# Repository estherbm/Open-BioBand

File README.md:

# Open-BioBand

    Open BioBand is a biometric Open Source wristband with BLE (Bluetooth
    Low Energy) connectivity used to non-invasive monitorization of patients
    and their environment. It measure several parameters such as pulse, SPO2,
    body temperature, motion activity, pressure, humidity, temperature...

    It allow developers to investigate and learn about wearables and biometric 
    sensors and artists to create new biological performances and projects.
    
    Created as final thesis Industrial Engineering project.

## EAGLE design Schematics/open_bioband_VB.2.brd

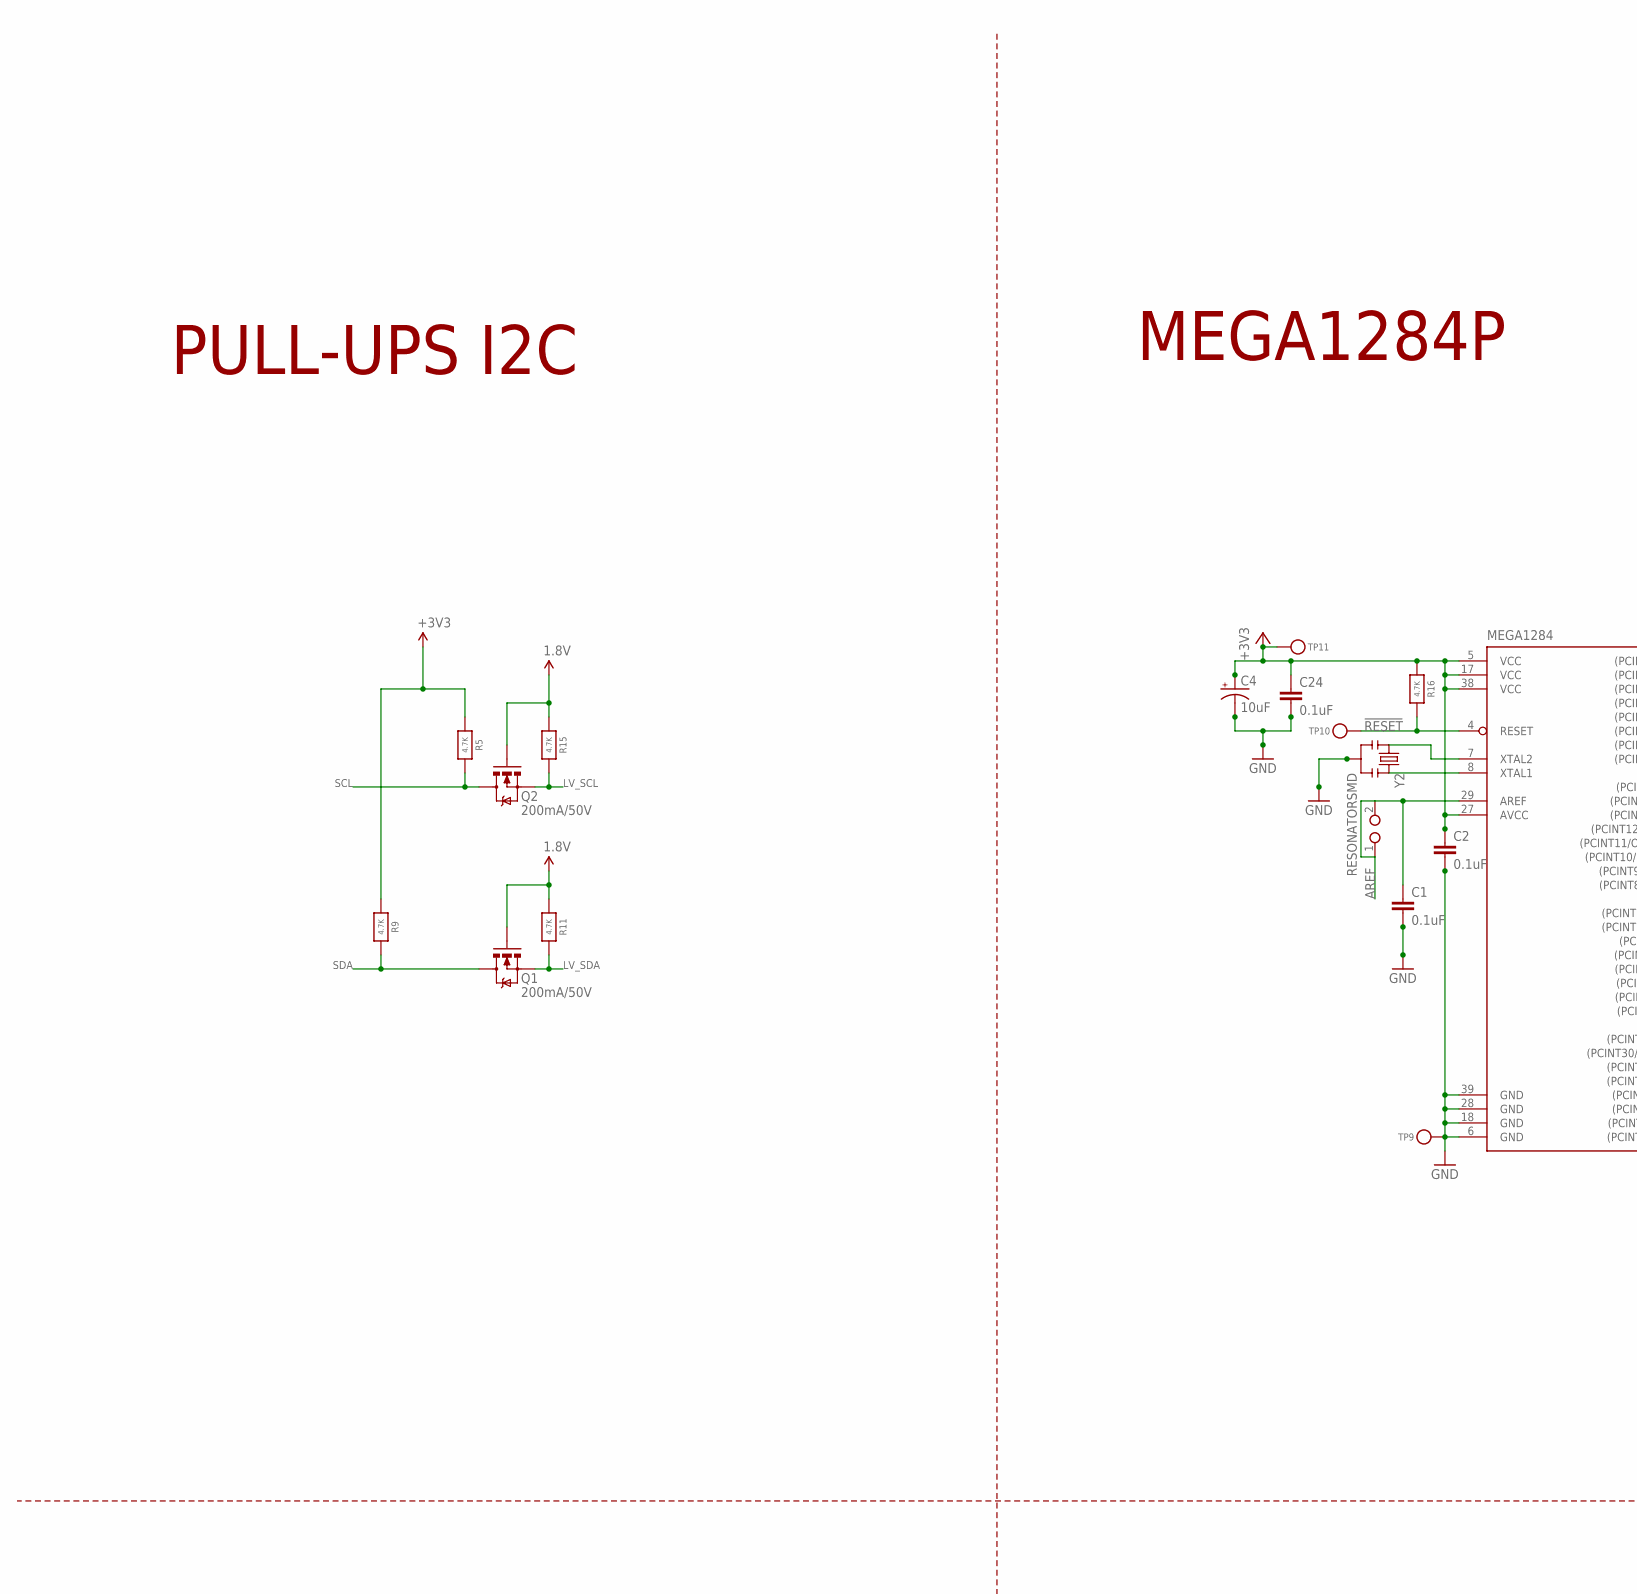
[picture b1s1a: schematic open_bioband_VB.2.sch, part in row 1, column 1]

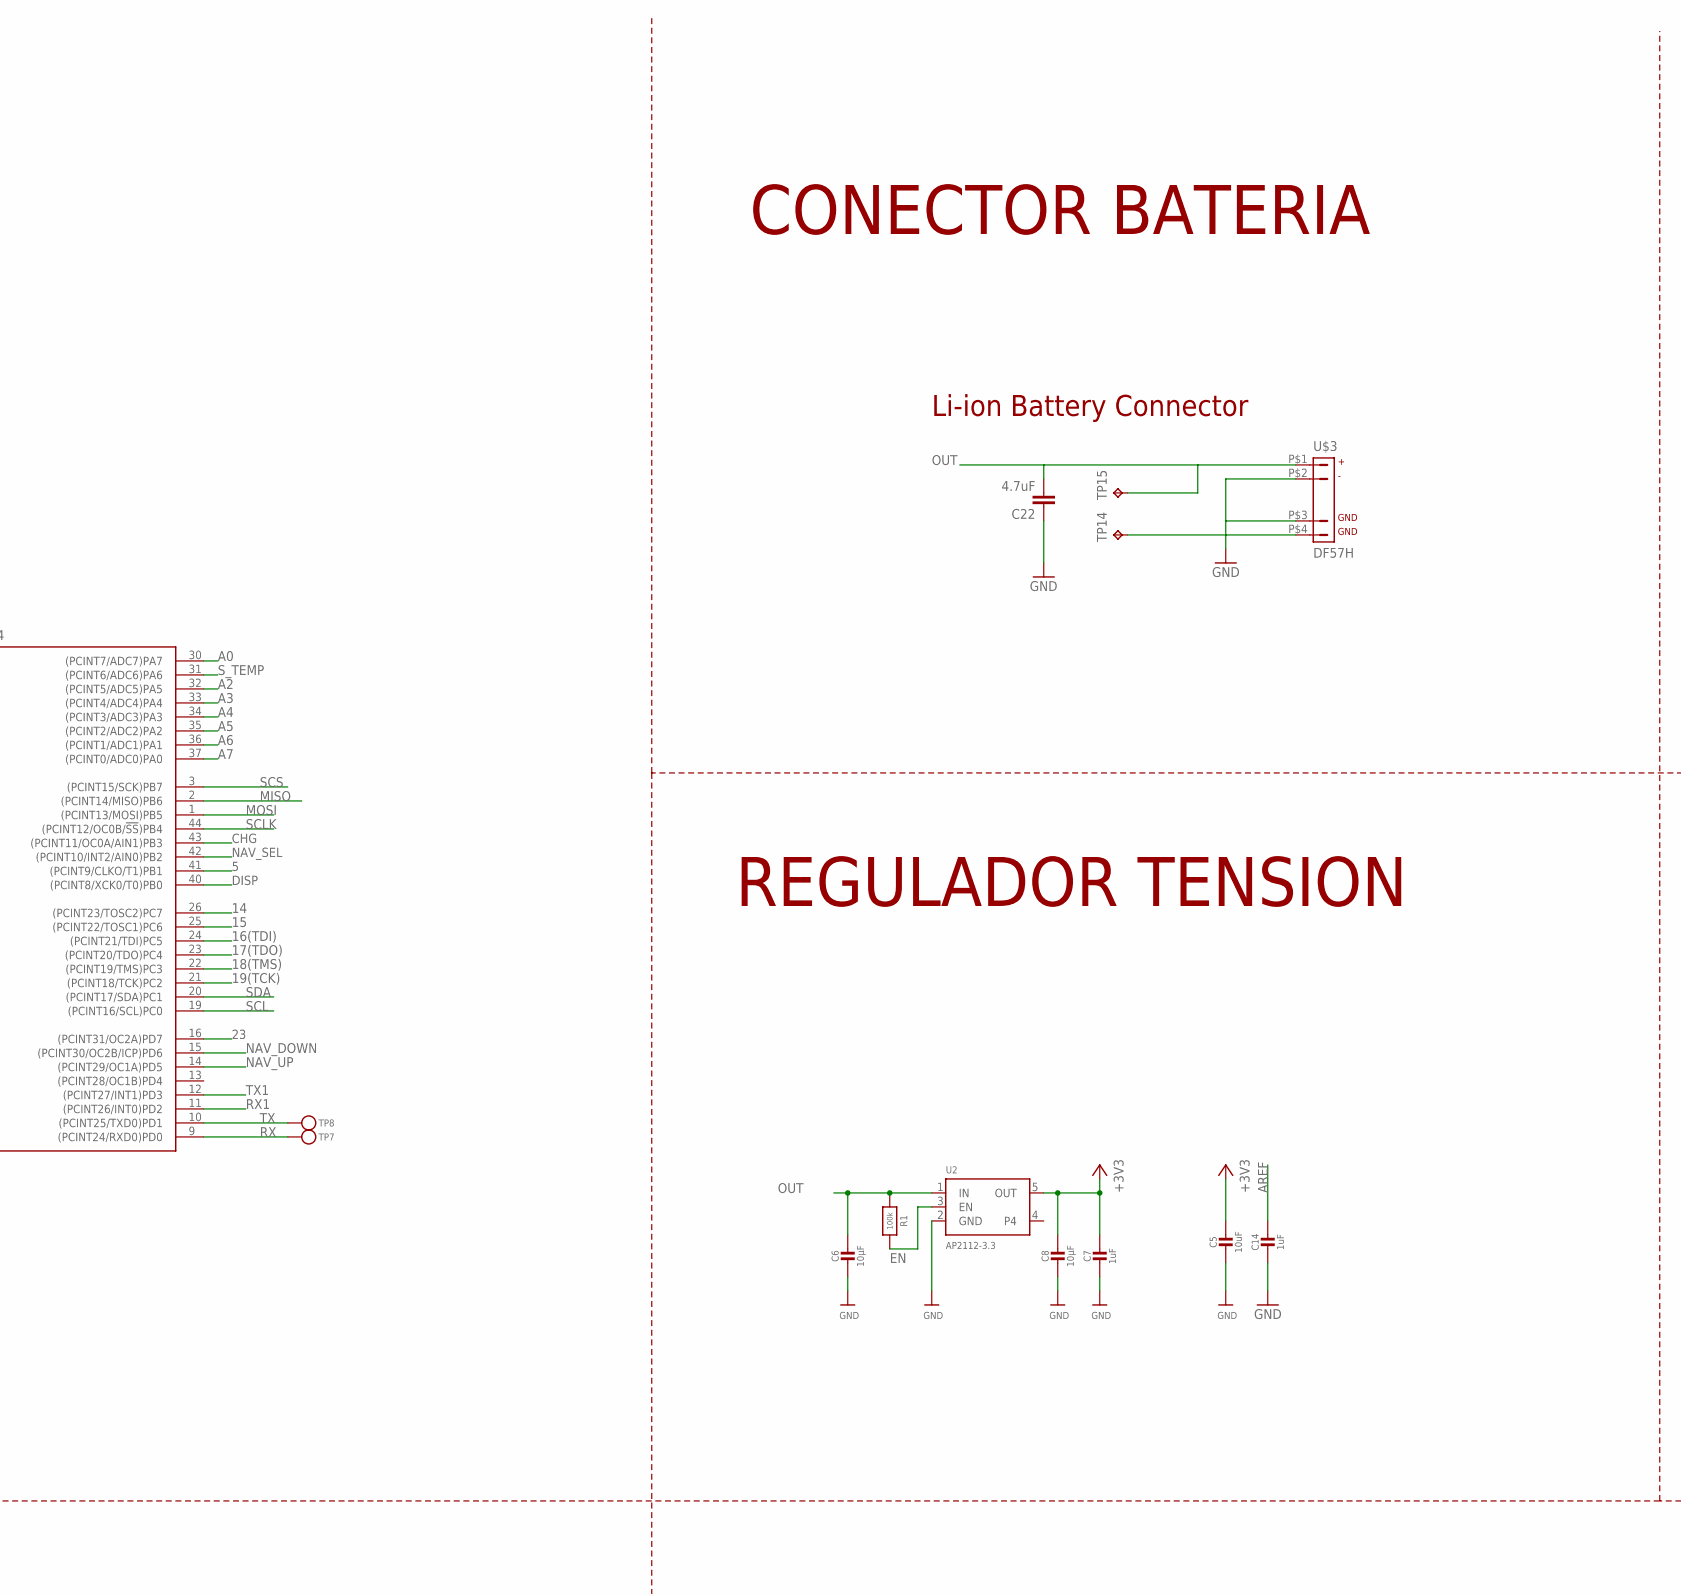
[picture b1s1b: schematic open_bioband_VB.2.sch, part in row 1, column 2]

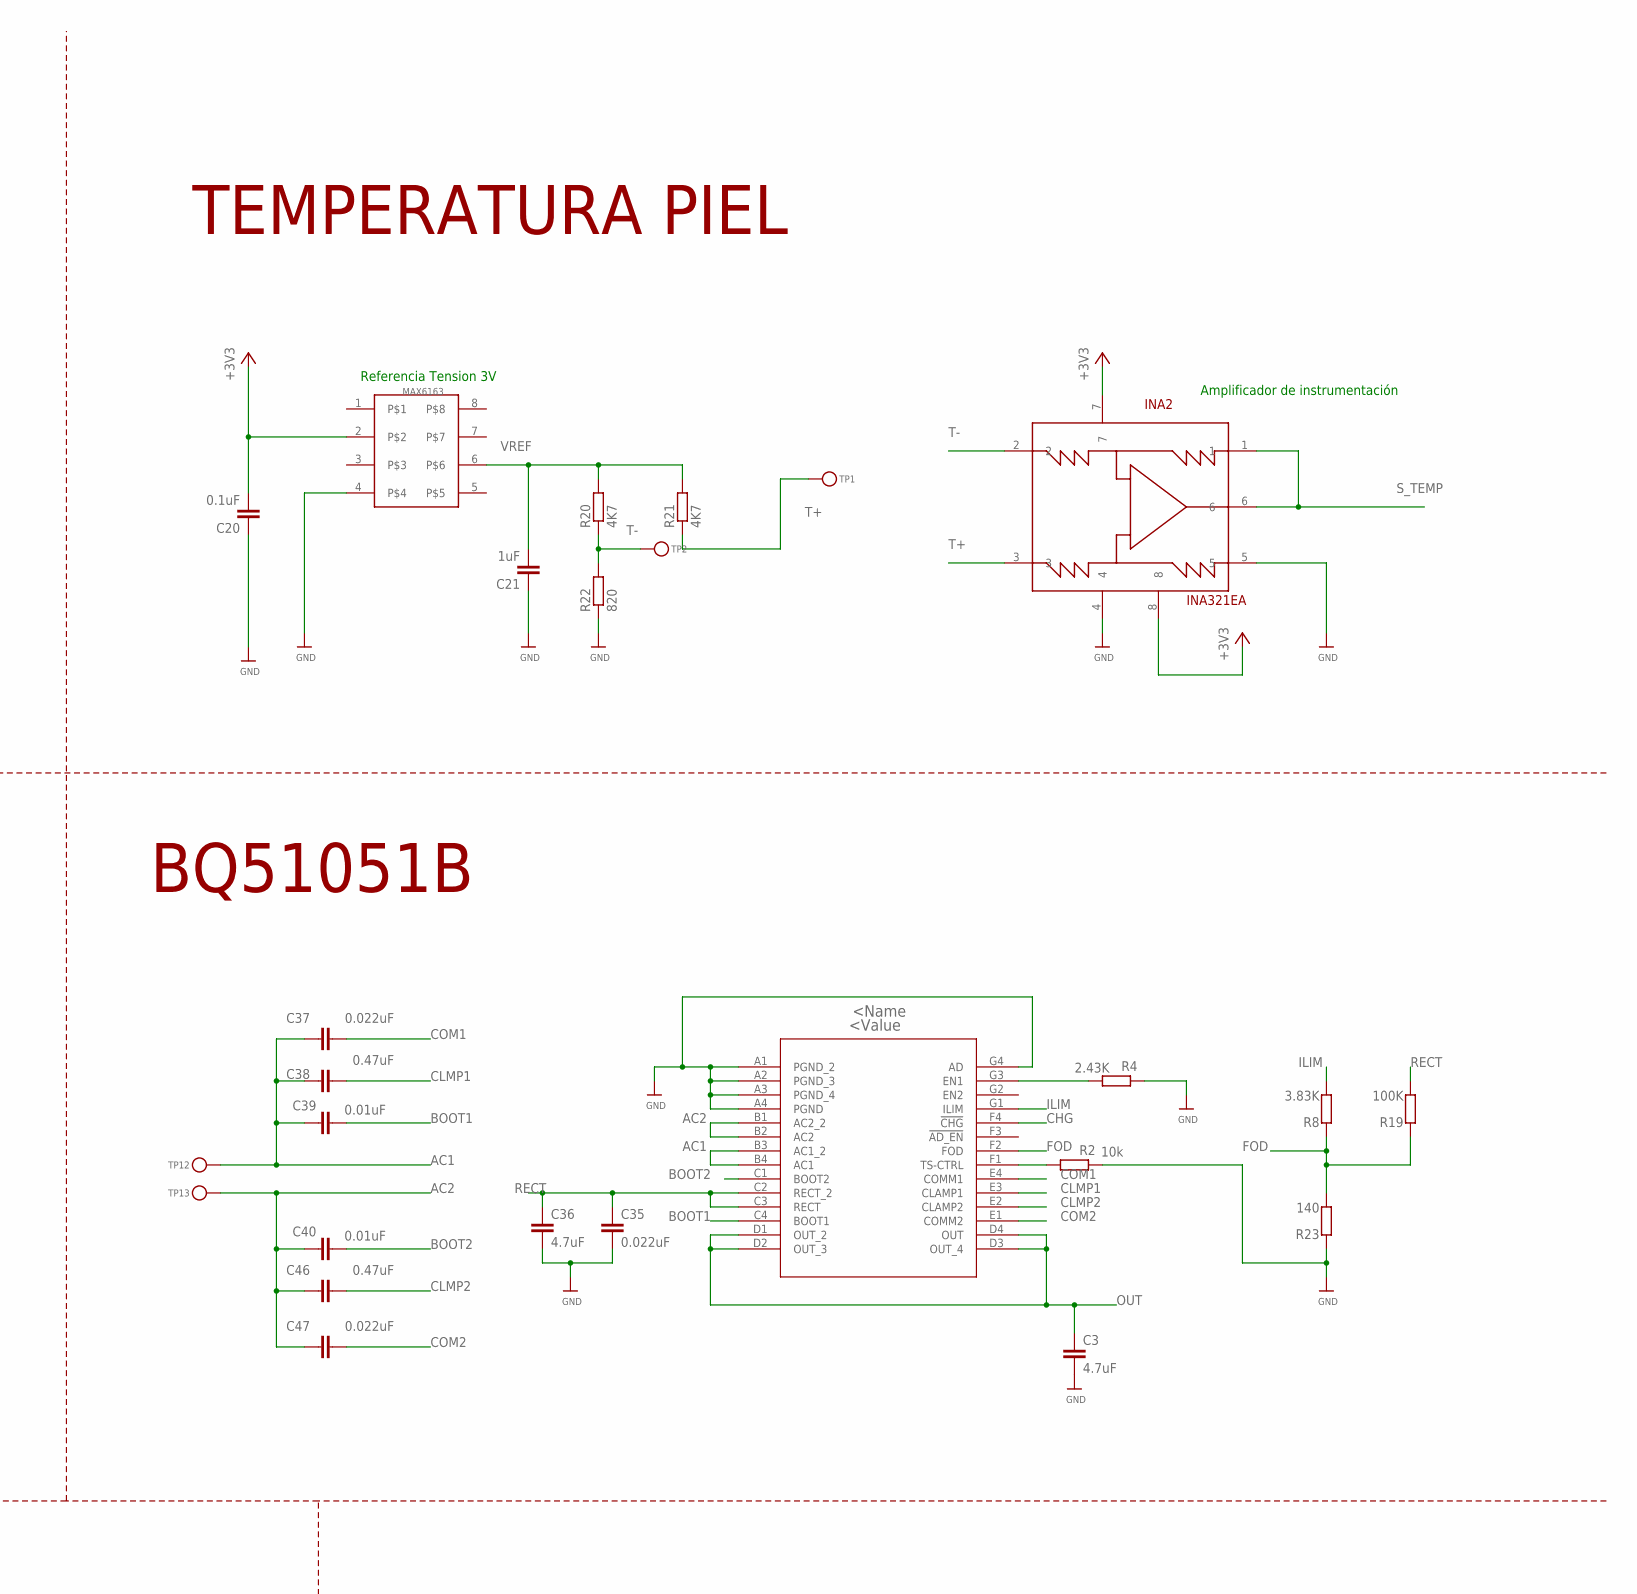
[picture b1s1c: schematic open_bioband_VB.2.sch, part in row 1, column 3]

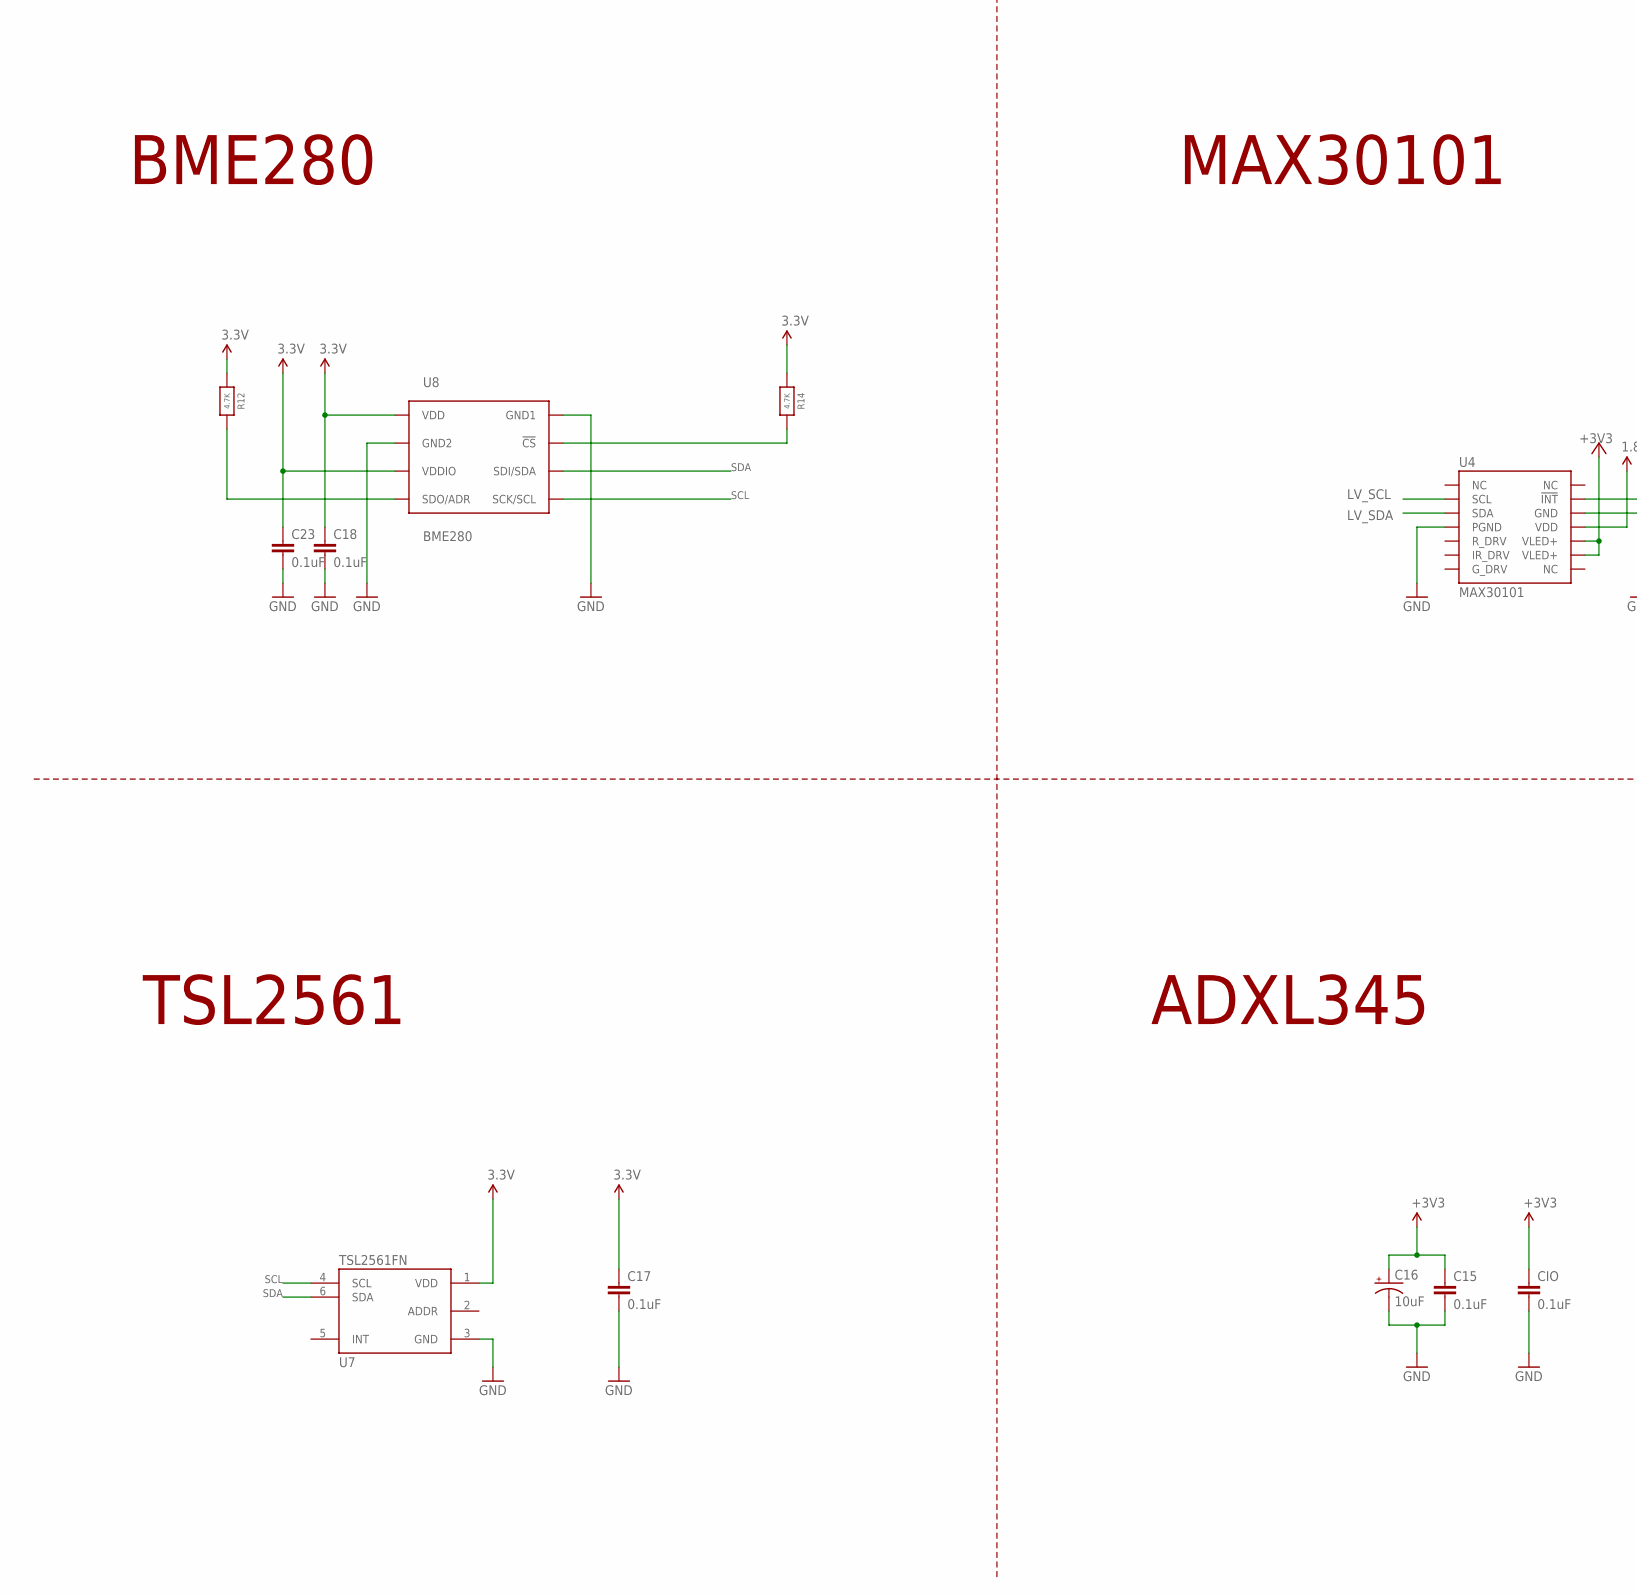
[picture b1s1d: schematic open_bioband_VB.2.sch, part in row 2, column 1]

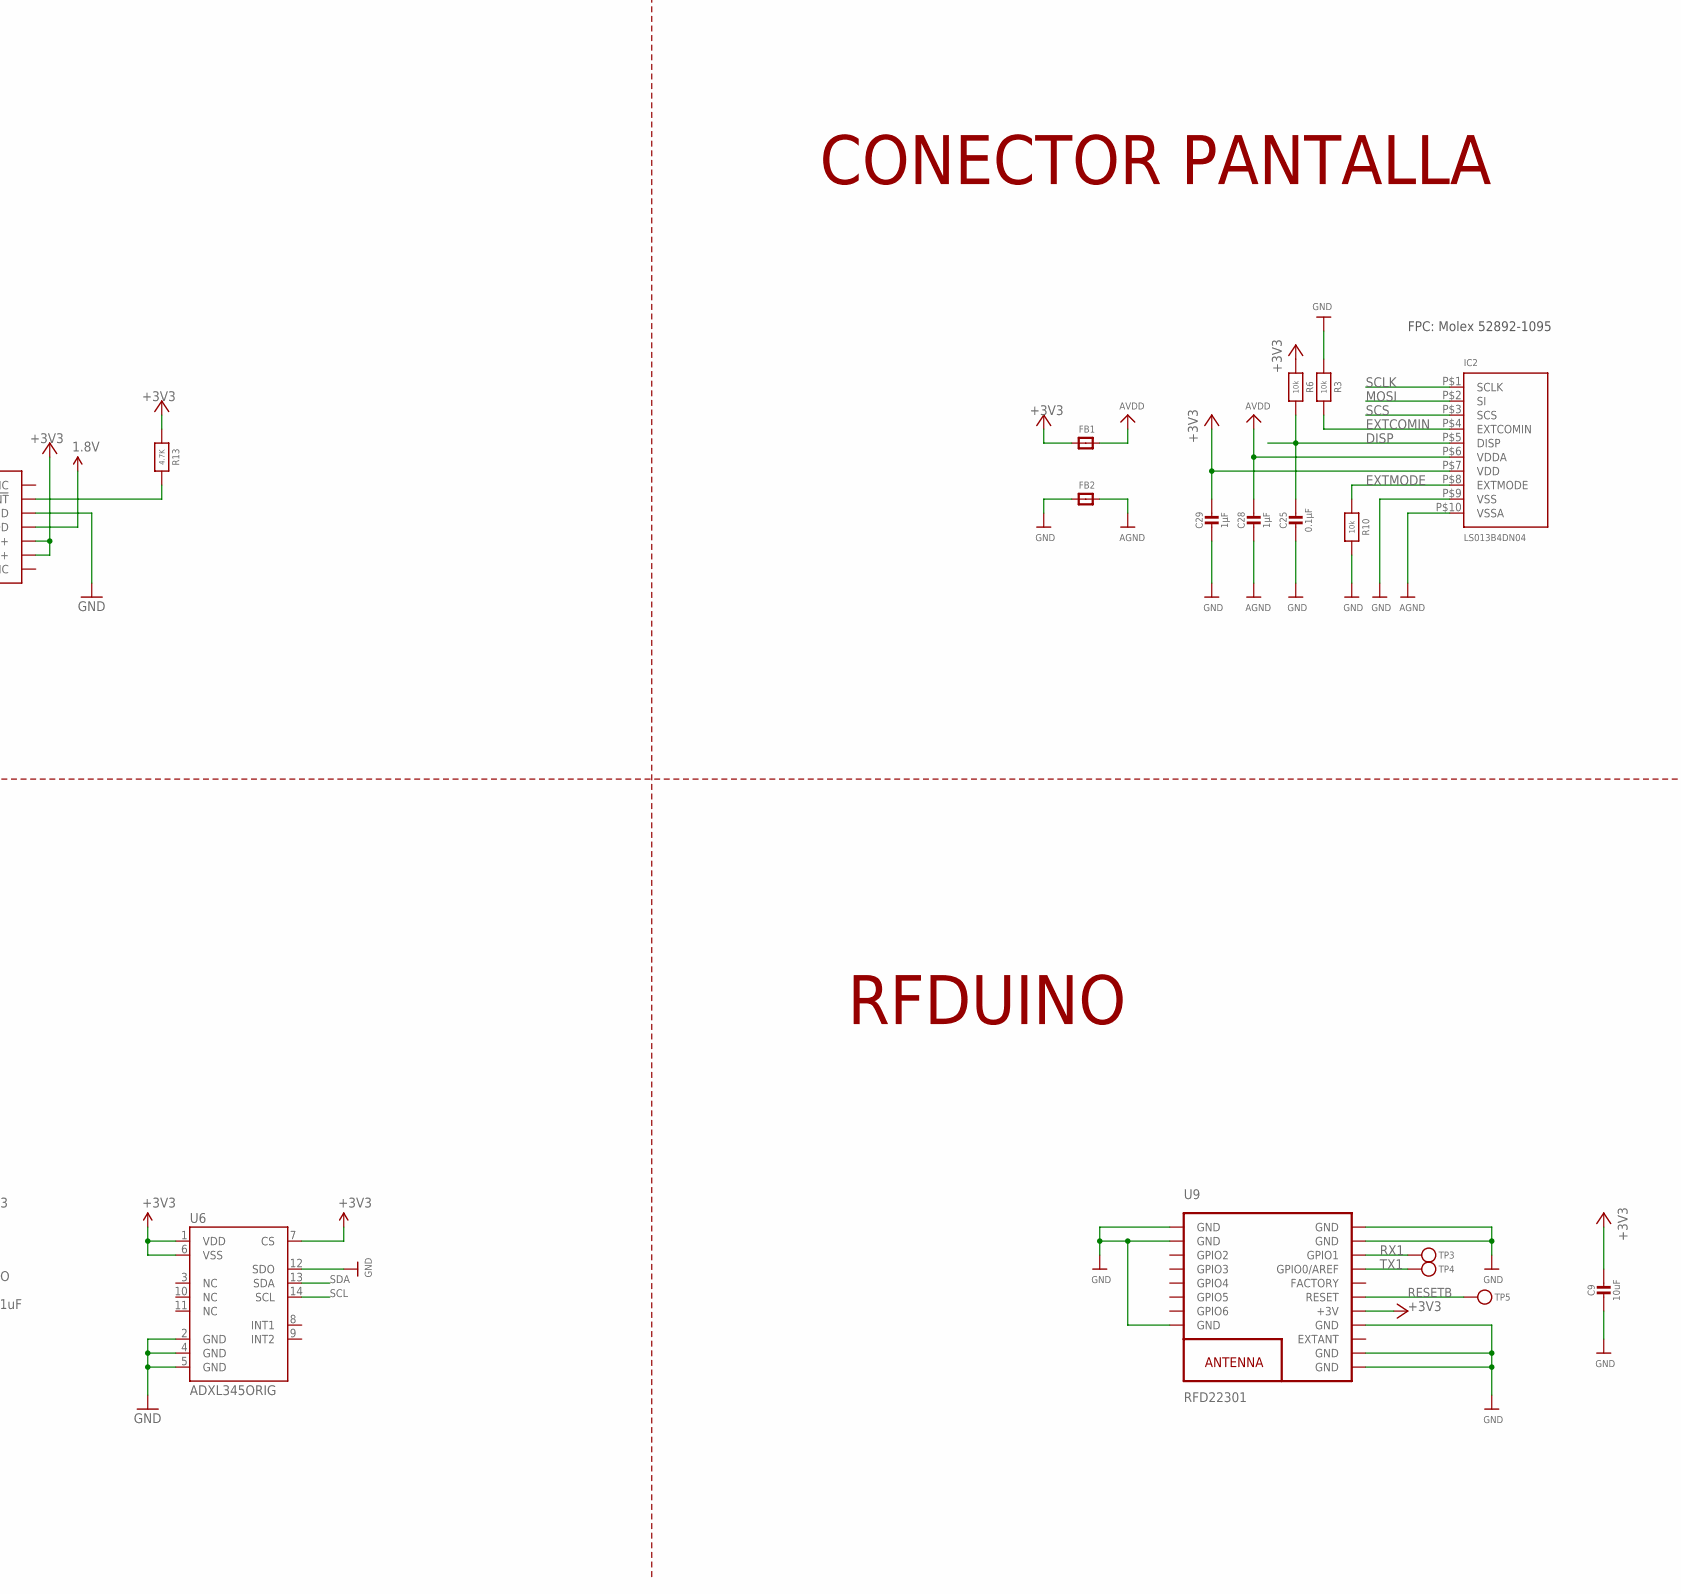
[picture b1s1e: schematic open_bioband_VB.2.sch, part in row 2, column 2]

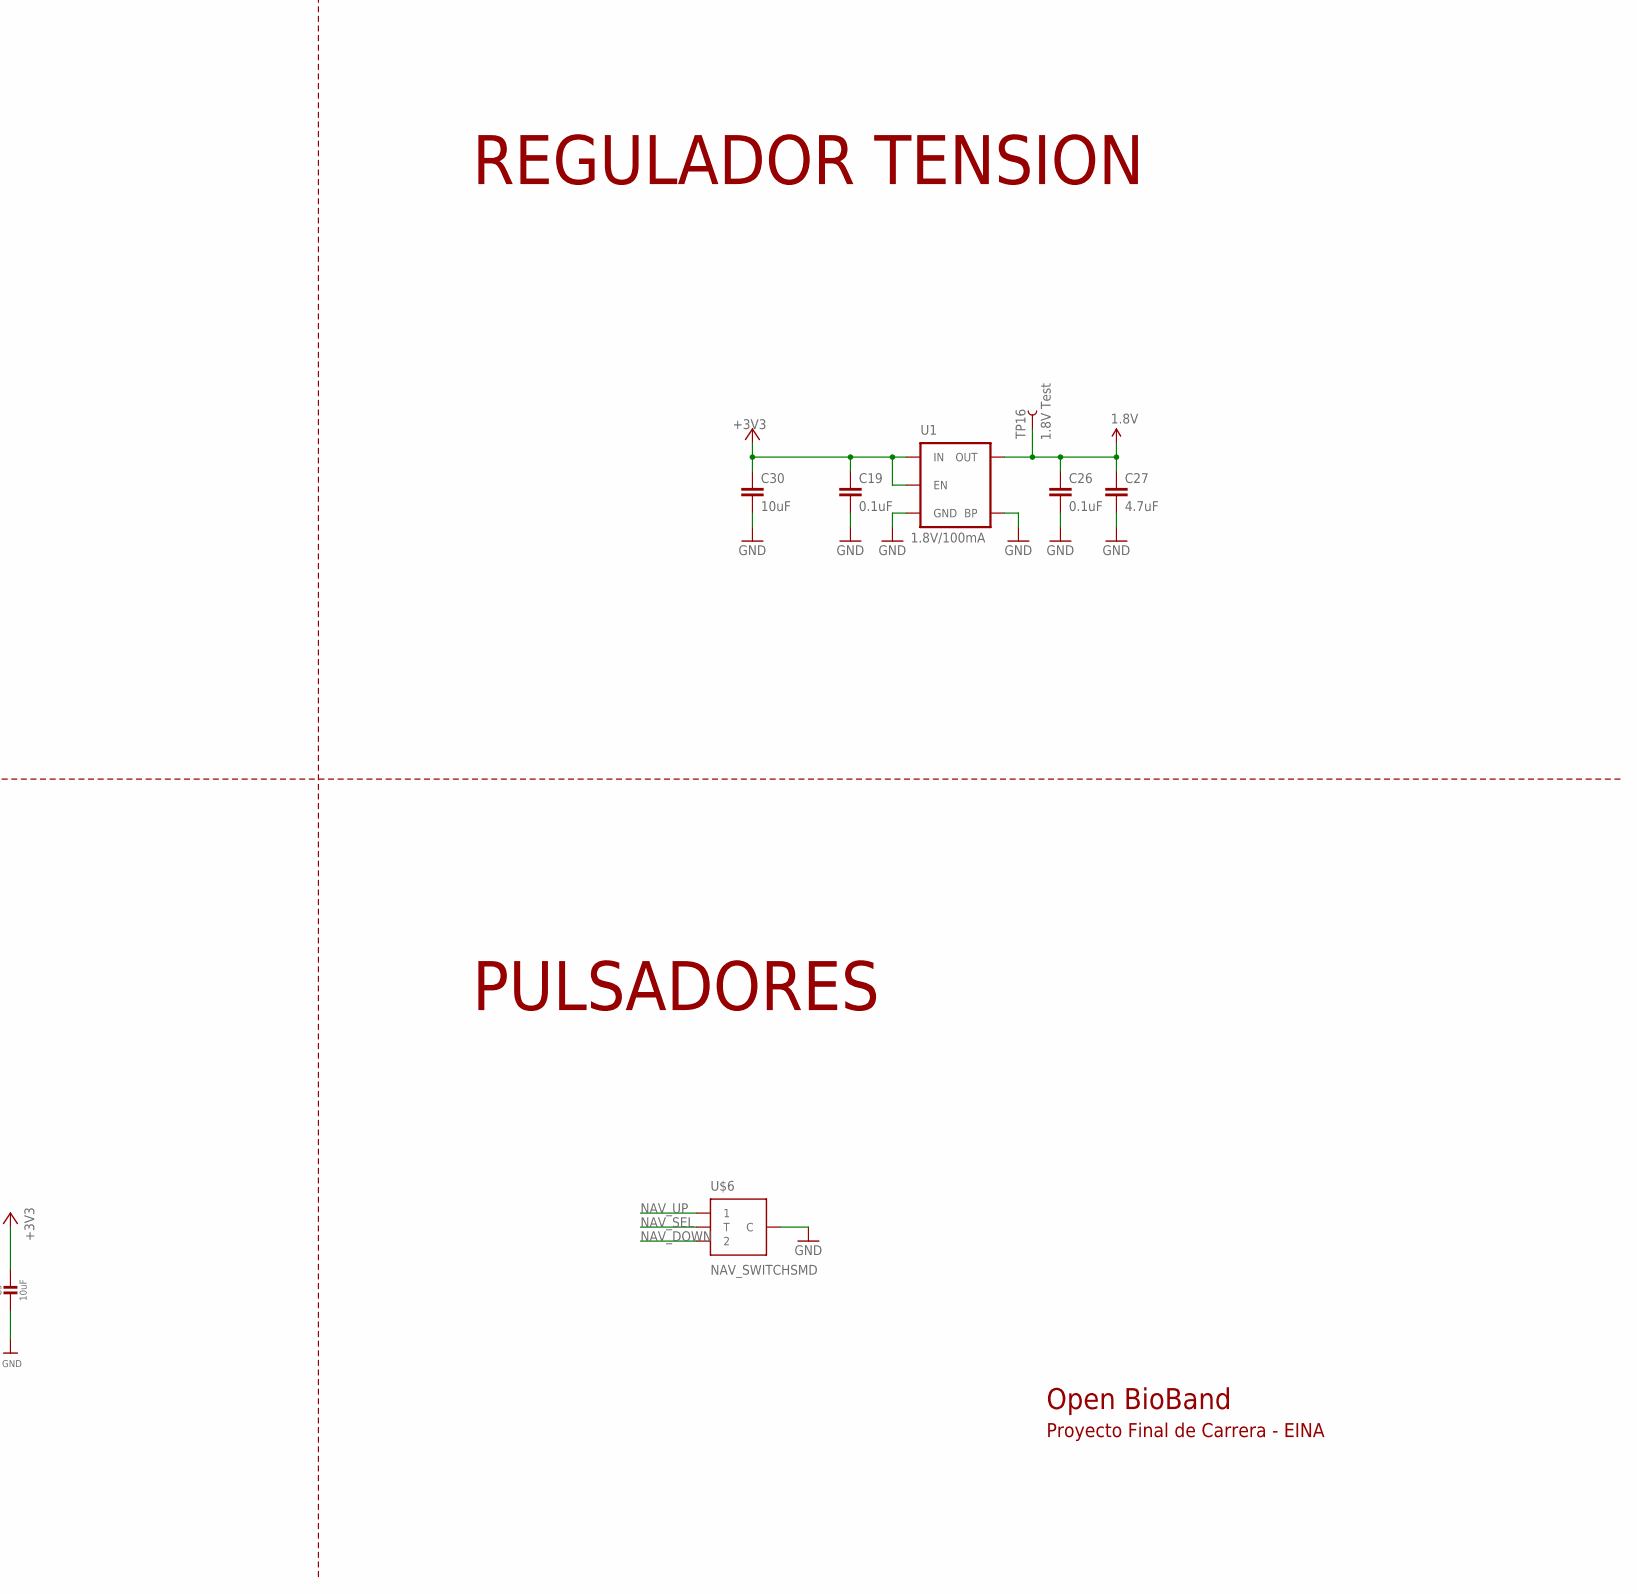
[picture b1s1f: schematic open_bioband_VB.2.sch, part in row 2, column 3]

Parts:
C1, C2, C15, C17, C18, C19, C23, C24, C26: 0.1uF; 0402-CAP
C3, C22, C36: 4.7uF; C0402
C4, C16: 10uF; EIA3216
C5, C9: 10uF; _0402
C6, C8: 10µF; _0402
C7, C14: 1uF; _0402
C20: 0.1uF; C0402
C21: 1uF; C0402
C25: 0.1µF; _0402
C27: 4.7uF; 0402-CAP
C28, C29: 1µF; _0402
C30: 10uF; 0402-CAP
C35, C37, C47: 0.022uF; C0402
C38, C46: 0.47uF; C0402
C39, C40: 0.01uF; C0402
CIO: 0.1uF; 0402-CAP
FB1, FB2: FERRITE_0402; _0402
IC2: LS013B4DN04; FPC_10PIN_52892-1095
INA2: INA321EA; MSOP08
MAX1: MAX6163; SO08
MEGA1284: ATMEGA644A; TQFP44
Q1, Q2: 200mA/50V; SOT23-3
R1: 100k; _0402
R2: 10k; R0402
R3, R6, R10: 10k; _0402
R4: 2.43K; R0402
R5, R9, R11, R12, R13, R14, R15, R16: 4.7K; _0402
R8: 3.83K; R0402
R19: 100K; R0402
R20, R21: 4K7; R0402
R22: 820; R0402
R23: 140; R0402
TP1, TP2, TP3, TP4, TP5, TP7, TP8, TP9, TP10, TP11, TP12, TP13: TESTPOINTROUND1.5MM; TESTPOINT_ROUND_1.5MM
TP14, TP15: TPB1,27; B1,27
TP16: 1.8V Test; PAD.03X.04
U1: 1.8V/100mA; SC70
U2: AP2112-3.3; SOT23-5
U3: BQ51003YFPT; YFP28
U4: MAX30101; OLGA-14
U6: ADXL345ORIG; LGA14
U7: TSL2561FN; FN-6
U8: BME280; BME280_LGA
U9: RFD22301
U$3: DF57H; DF57H-2P
U$5: JUMPER1-1
U$6: NAV_SWITCHSMD; NAV_SWITCH
Y2: RESONATORSMD; RESONATOR-SMD

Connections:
1.8V: C26.1, C27.1, Q1.1 (G), Q2.1 (G), R11.1, R15.1, TP16.P$1, U1.5 (OUT), U4.11 (VDD)
5: MEGA1284.41 ((PCINT9/CLKO/T1)PB1)
14: MEGA1284.26 ((PCINT23/TOSC2)PC7)
15: MEGA1284.25 ((PCINT22/TOSC1)PC6)
16(TDI): MEGA1284.24 ((PCINT21/TDI)PC5)
17(TDO): MEGA1284.23 ((PCINT20/TDO)PC4)
18(TMS): MEGA1284.22 ((PCINT19/TMS)PC3)
19(TCK): MEGA1284.21 ((PCINT18/TCK)PC2)
23: MEGA1284.16 ((PCINT31/OC2A)PD7)
!CS: R14.2, U8.P$2 (!CS)
!INT: R13.2, U4.13 (!INT)
!RESET: MEGA1284.4 (RESET), R16.2, TP10.P$1
+3V3: C2.1, C4.A (+), C5.1, C7.1, C8.1, C9.1, C15.1, C16.A (+), C17.1, C19.1, C20.2, C24.1, C29.1, C30.1, CIO.1, FB1.1, IC2.P$7 (VDD), INA2.7, INA2.8, MAX1.2, MEGA1284.5 (VCC), MEGA1284.17 (VCC), MEGA1284.27 (AVCC), MEGA1284.38 (VCC), R5.1, R6.1, R9.1, R13.1, R16.1, TP11.P$1, U1.1 (IN), U1.3 (EN), U2.5 (OUT), U4.9 (VLED+), U4.10 (VLED+), U6.1 (VDD), U6.6 (VSS), U6.7 (CS), U7.1 (VDD), U9.13 (+3V)
A0: MEGA1284.30 ((PCINT7/ADC7)PA7)
A2: MEGA1284.32 ((PCINT5/ADC5)PA5)
A3: MEGA1284.33 ((PCINT4/ADC4)PA4)
A4: MEGA1284.34 ((PCINT3/ADC3)PA3)
A5: MEGA1284.35 ((PCINT2/ADC2)PA2)
A6: MEGA1284.36 ((PCINT1/ADC1)PA1)
A7: MEGA1284.37 ((PCINT0/ADC0)PA0)
AC1: C37.1, C38.1, C39.1, TP12.P$1, U3.B3 (AC1_2), U3.B4 (AC1)
AC2: C40.1, C46.1, C47.1, TP13.P$1, U3.B1 (AC2_2), U3.B2 (AC2)
AGND: C28.2, FB2.2, IC2.P$10 (VSSA)
AREF: C1.1, C14.1, MEGA1284.29 (AREF), U$5.1, U$5.2
AVDD: C28.1, FB1.2, IC2.P$6 (VDDA)
BOOT1: C39.2, U3.C4 (BOOT1)
BOOT2: C40.2, U3.C1 (BOOT2)
CHG: MEGA1284.43 ((PCINT11/OC0A/AIN1)PB3), U3.F4 (!CHG)
CLMP1: C38.2, U3.E3 (CLAMP1)
CLMP2: C46.2, U3.E2 (CLAMP2)
COM1: C37.2, U3.E4 (COMM1)
COM2: C47.2, U3.E1 (COMM2)
DISP: C25.1, IC2.P$5 (DISP), MEGA1284.40 ((PCINT8/XCK0/T0)PB0), R6.2
EN: R1.2, U2.3 (EN)
EXTCOMIN: IC2.P$4 (EXTCOMIN), R3.2
EXTMODE: IC2.P$8 (EXTMODE), R10.1
FOD: R8.1, R19.1, R23.2, U3.F2 (FOD)
GND: C1.2, C2.2, C3.2, C4.C (-), C5.2, C6.2, C7.2, C8.2, C9.2, C14.2, C15.2, C16.C (-), C17.2, C18.2, C19.2, C20.1, C21.1, C22.1, C23.2, C24.2, C25.2, C26.2, C27.2, C29.2, C30.2, C35.2, C36.2, CIO.2, FB2.1, IC2.P$9 (VSS), INA2.4, INA2.5, MAX1.4, MEGA1284.6 (GND), MEGA1284.18 (GND), MEGA1284.28 (GND), MEGA1284.39 (GND), R2.2, R3.1, R4.2, R10.2, R22.1, R23.1, TP9.P$1, TP14.TP, U1.2 (GND), U1.4 (BP), U2.2 (GND), U3.A1 (PGND_2), U3.A2 (PGND_3), U3.A3 (PGND_4), U3.A4 (PGND), U3.G4 (AD), U4.4 (PGND), U4.12 (GND), U6.2 (GND), U6.4 (GND), U6.5 (GND), U6.12 (SDO), U7.3 (GND), U8.P$1 (GND1), U8.P$7 (GND2), U9.1 (GND), U9.2 (GND), U9.8 (GND), U9.9 (GND), U9.10 (GND), U9.12 (GND), U9.18 (GND), U9.19 (GND), U$3.P$2 (2), U$3.P$3 (5), U$3.P$4 (6), U$6.C, Y2.2
ILIM: R8.2, U3.G1 (ILIM)
LV_SCL: Q2.2 (S), R15.2, U4.2 (SCL)
LV_SDA: Q1.2 (S), R11.2, U4.3 (SDA)
MISO: MEGA1284.2 ((PCINT14/MISO)PB6)
MOSI: IC2.P$2 (SI), MEGA1284.1 ((PCINT13/MOSI)PB5)
unnamed: MEGA1284.7 (XTAL2), Y2.1
unnamed: R4.1, U3.G3 (EN1)
unnamed: MEGA1284.8 (XTAL1), Y2.3
unnamed: R2.1, U3.F1 (TS-CTRL)
NAV_DOWN: MEGA1284.15 ((PCINT30/OC2B/ICP)PD6), U$6.2
NAV_SEL: MEGA1284.42 ((PCINT10/INT2/AIN0)PB2), U$6.T
NAV_UP: MEGA1284.14 ((PCINT29/OC1A)PD5), U$6.1
OUT: C3.1, C6.1, C22.2, R1.1, TP15.TP, U2.1 (IN), U3.D1 (OUT_2), U3.D2 (OUT_3), U3.D3 (OUT_4), U3.D4 (OUT), U$3.P$1 (1)
RECT: C35.1, C36.1, R19.2, U3.C2 (RECT_2)
RESETB: TP5.P$1, U9.14 (RESET)
RX: MEGA1284.9 ((PCINT24/RXD0)PD0), TP7.P$1
RX1: MEGA1284.11 ((PCINT26/INT0)PD2), TP3.P$1, U9.17 (GPIO1)
SCL: MEGA1284.19 ((PCINT16/SCL)PC0), Q2.3 (D), R5.2, U6.14 (SCL), U7.4 (SCL), U8.P$4 (SCK/SCL)
SCLK: IC2.P$1 (SCLK), MEGA1284.44 ((PCINT12/OC0B/!SS!)PB4)
SCS: IC2.P$3 (SCS), MEGA1284.3 ((PCINT15/SCK)PB7)
SDA: MEGA1284.20 ((PCINT17/SDA)PC1), Q1.3 (D), R9.2, U6.13 (SDA), U7.6 (SDA), U8.P$3 (SDI/SDA)
SDO/ADR: R12.2, U8.P$5 (SDO/ADR)
S_TEMP: INA2.1, INA2.6, MEGA1284.31 ((PCINT6/ADC6)PA6)
T+: INA2.3, R21.1, TP1.P$1
T-: INA2.2, R20.1, R22.2, TP2.P$1
TX: MEGA1284.10 ((PCINT25/TXD0)PD1), TP8.P$1
TX1: MEGA1284.12 ((PCINT27/INT1)PD3), TP4.P$1, U9.16 (GPIO0/AREF)
VCC: C18.1, C23.1, R12.1, R14.1, U8.P$6 (VDDIO), U8.P$8 (VDD)
VREF: C21.2, MAX1.6, R20.2, R21.2

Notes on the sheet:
FPC: Molex 52892-1095
Referencia Tension 3V
Amplificador de instrumentación
Li-ion Battery Connector
Open BioBand
Proyecto Final de Carrera - EINA
TSL2561
ADXL345
RFDUINO
MAX30101
CONECTOR PANTALLA
BME280
REGULADOR TENSION
PULL-UPS I2C
MEGA1284P
CONECTOR BATERIA
BQ51051B
TEMPERATURA PIEL
PULSADORES

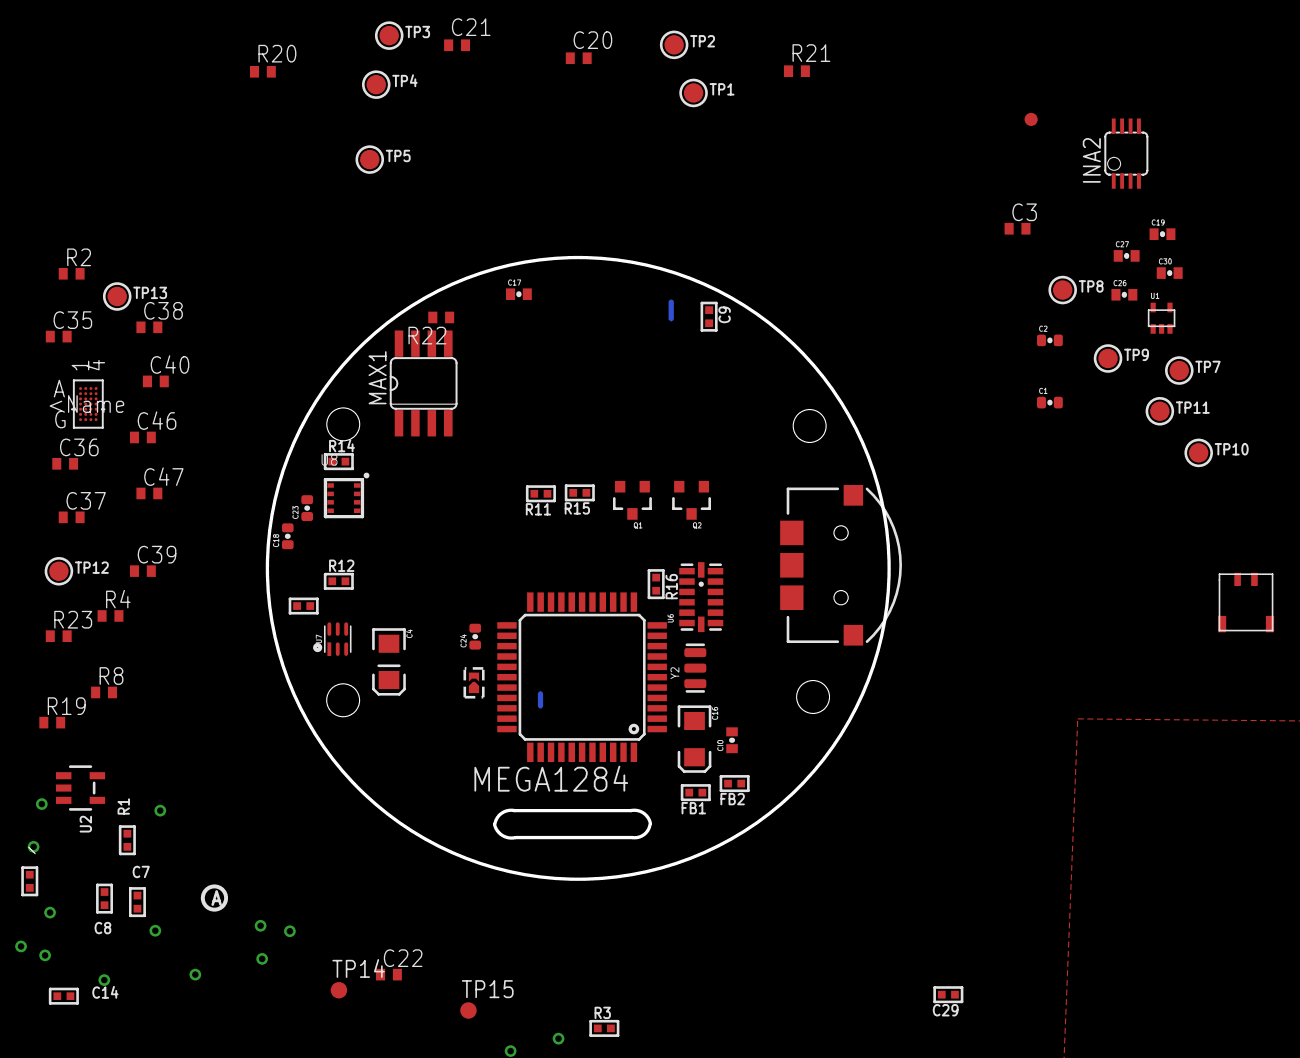
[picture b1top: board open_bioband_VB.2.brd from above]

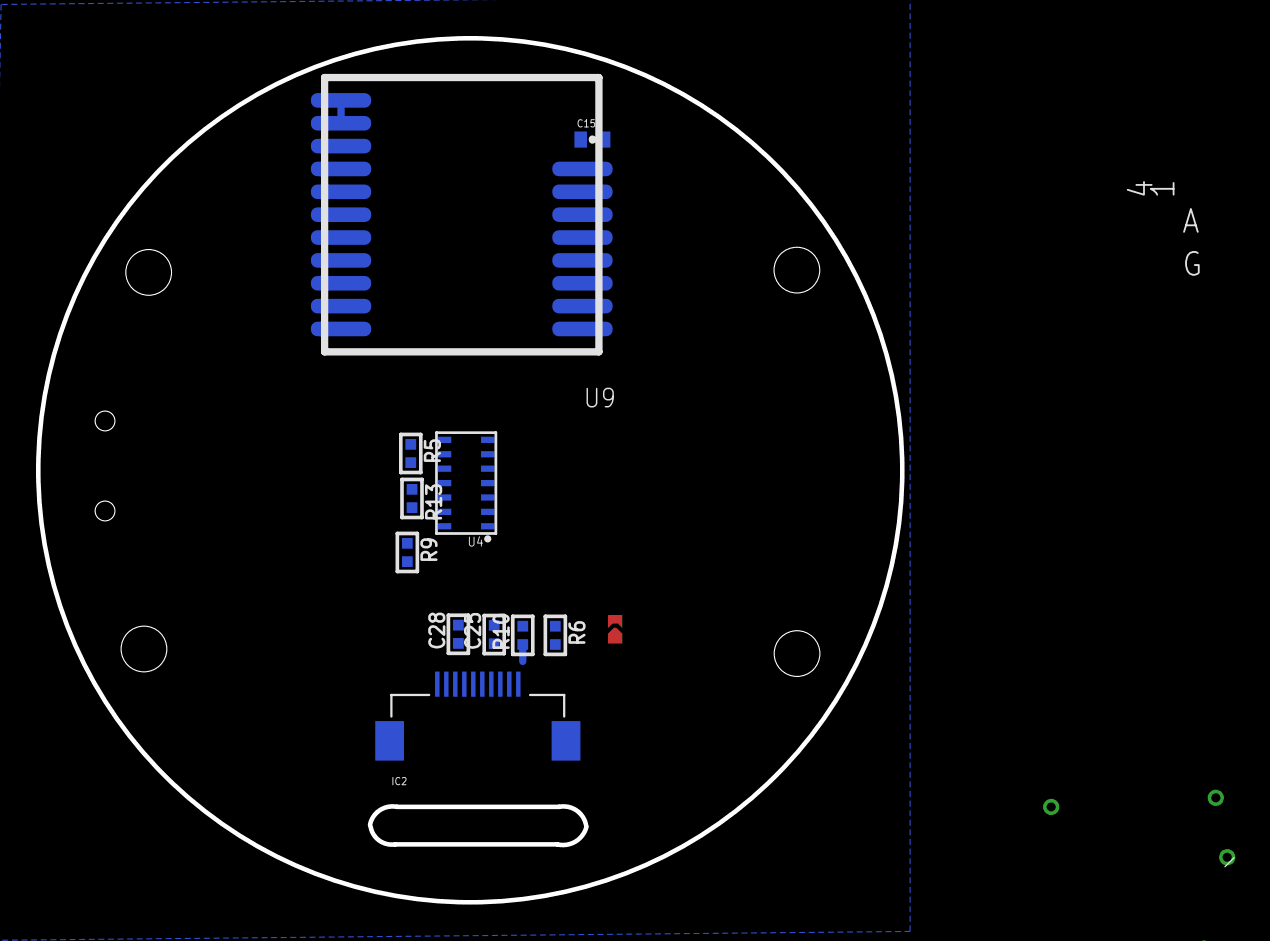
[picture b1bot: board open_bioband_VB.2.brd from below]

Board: 2 copper layers, 66.3 x 48.0 mm, 91 parts (11 on the bottom side), 51 nets.

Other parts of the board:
U$25: PCBFEAT-REV-040

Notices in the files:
parts and their libraries:
microbuilder: This work is placed in the public domain, and may be freely used for commercial and non-commercial work with the following conditions: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
SparkFun-Capacitors: Licensing: Creative Commons ShareAlike 4.0 International - https://creativecommons.org/licenses/by-sa/4.0
